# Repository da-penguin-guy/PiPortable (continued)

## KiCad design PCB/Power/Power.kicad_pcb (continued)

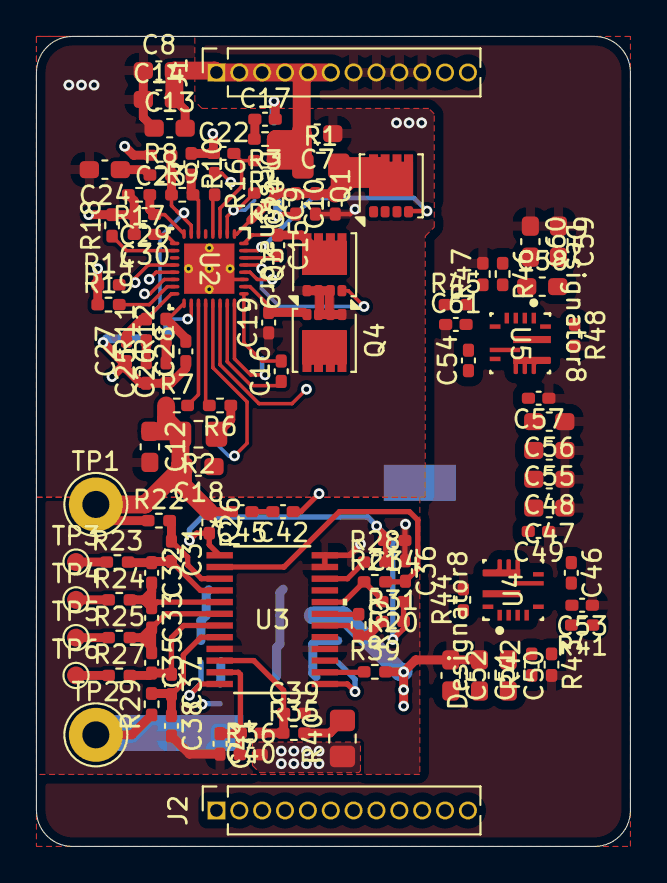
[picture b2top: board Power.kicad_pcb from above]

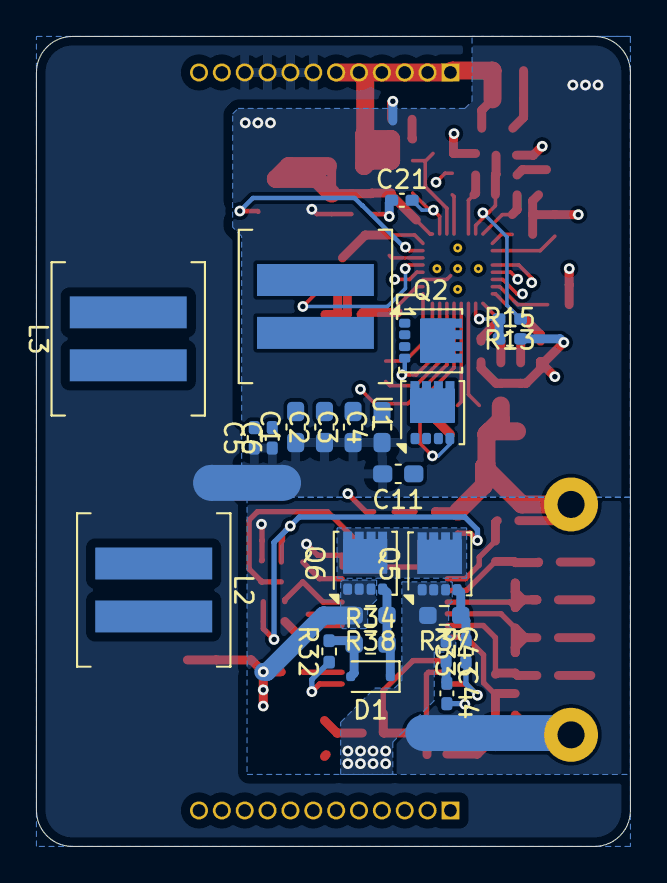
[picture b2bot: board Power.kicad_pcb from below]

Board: 6 copper layers, 33.0 x 45.0 mm, 134 parts (27 on the bottom side), 82 nets.

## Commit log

2025-04-09 Edited Readme and Renamed Source Folder
2025-04-09 Re-Integreated IO
2025-04-12 Added Venv
2025-04-13 Added PCB Schematics
    I just combined them. They WILL NOT actually function.
2025-04-15 reworded readme
2025-04-17 Added .gitignore
2025-04-22 Added pyLint
2025-04-22 Added documentation to helper.py and started changing pathing
2025-04-23 Redid everything regarding paths. Will it work? Who knows
2025-04-23 Updated comments in helper.py
2025-04-26 Updated PCB
